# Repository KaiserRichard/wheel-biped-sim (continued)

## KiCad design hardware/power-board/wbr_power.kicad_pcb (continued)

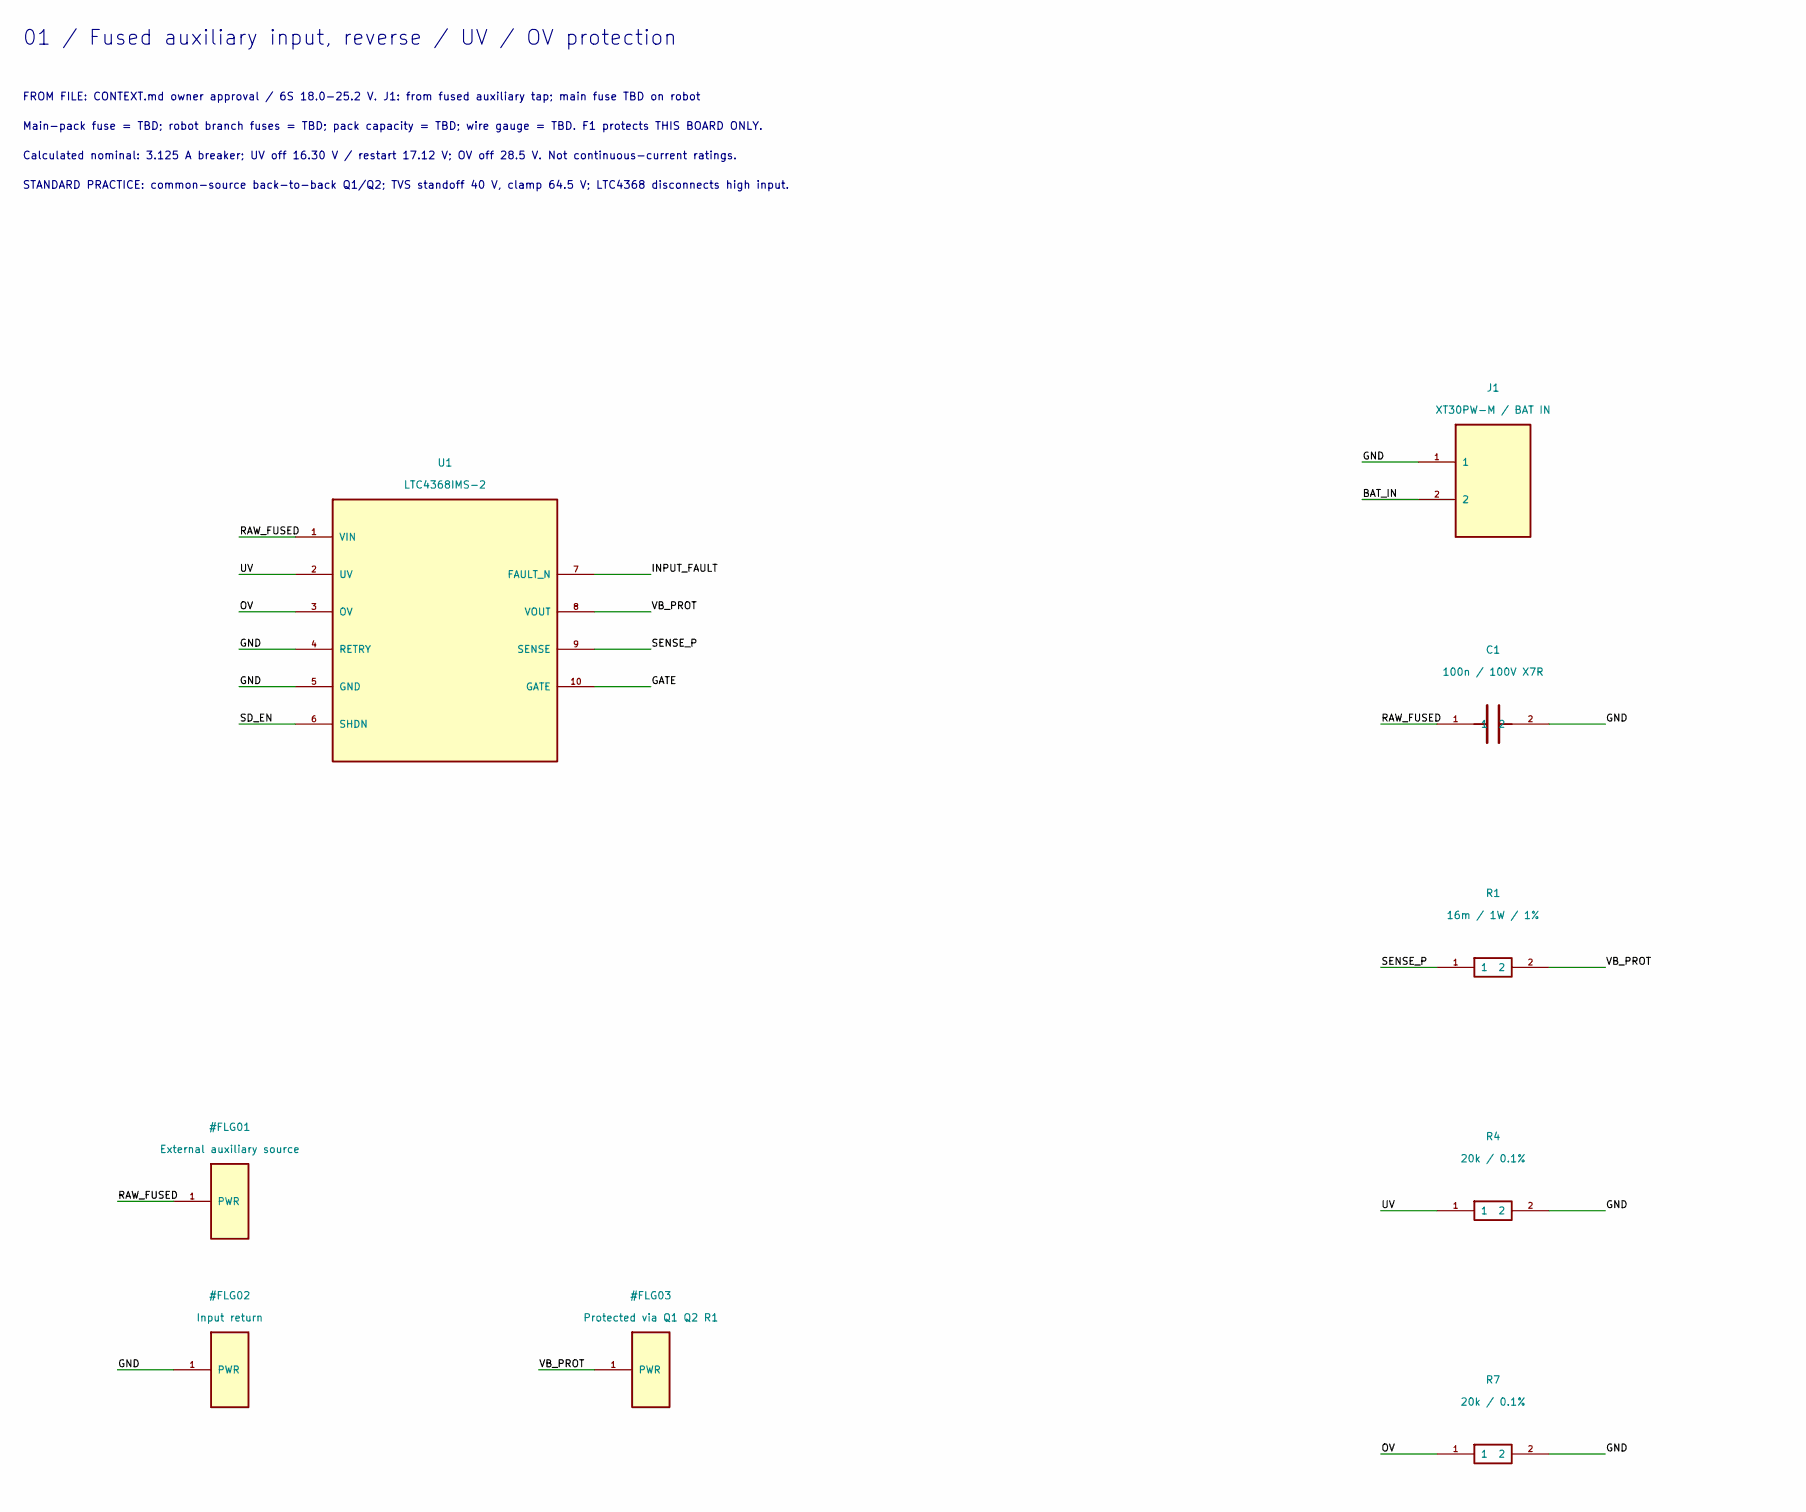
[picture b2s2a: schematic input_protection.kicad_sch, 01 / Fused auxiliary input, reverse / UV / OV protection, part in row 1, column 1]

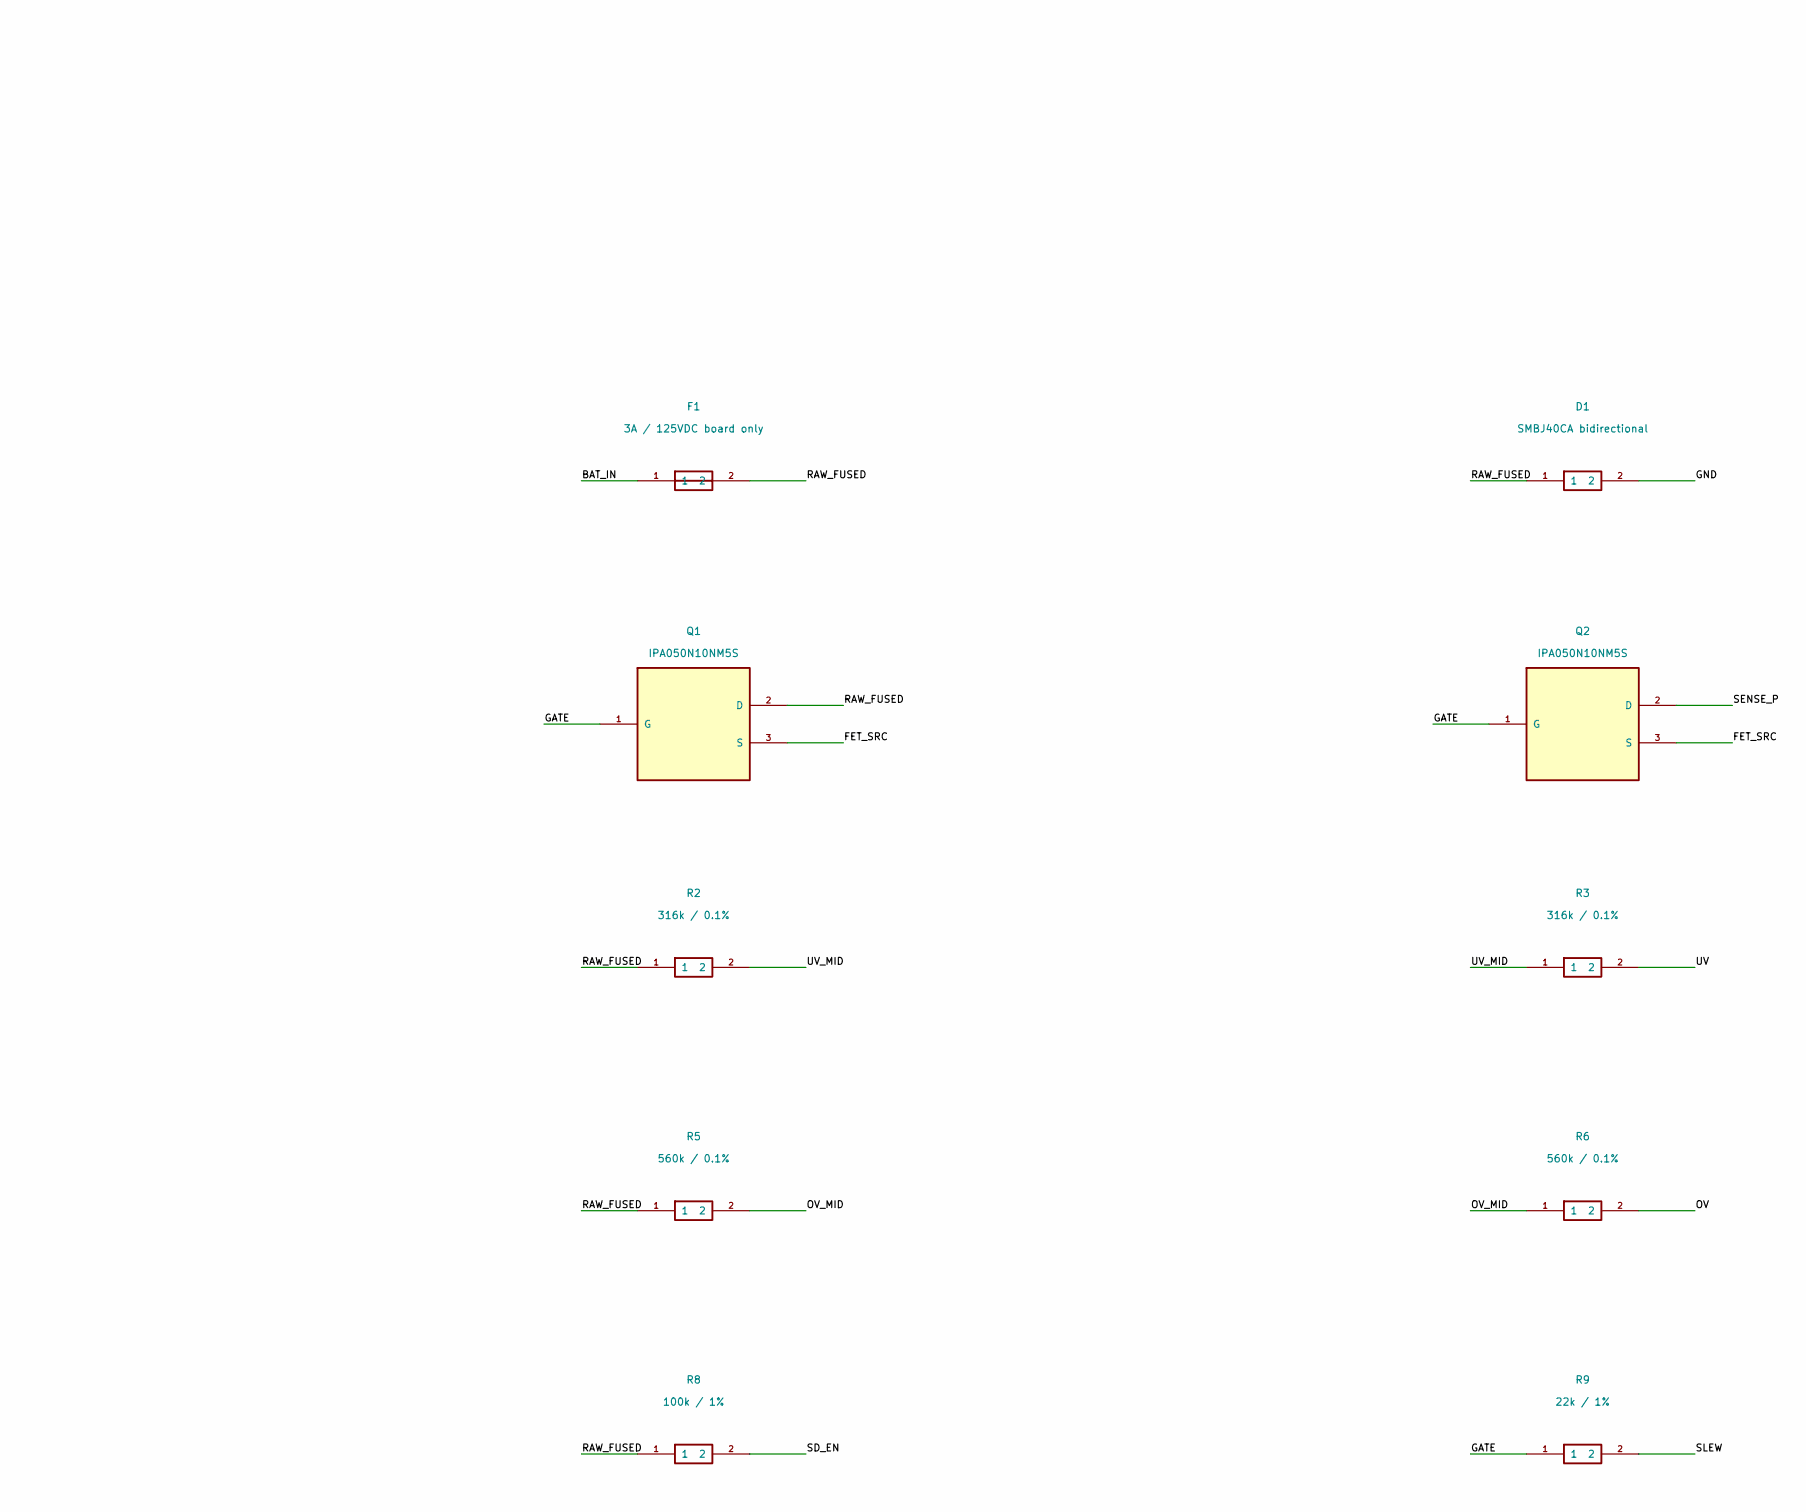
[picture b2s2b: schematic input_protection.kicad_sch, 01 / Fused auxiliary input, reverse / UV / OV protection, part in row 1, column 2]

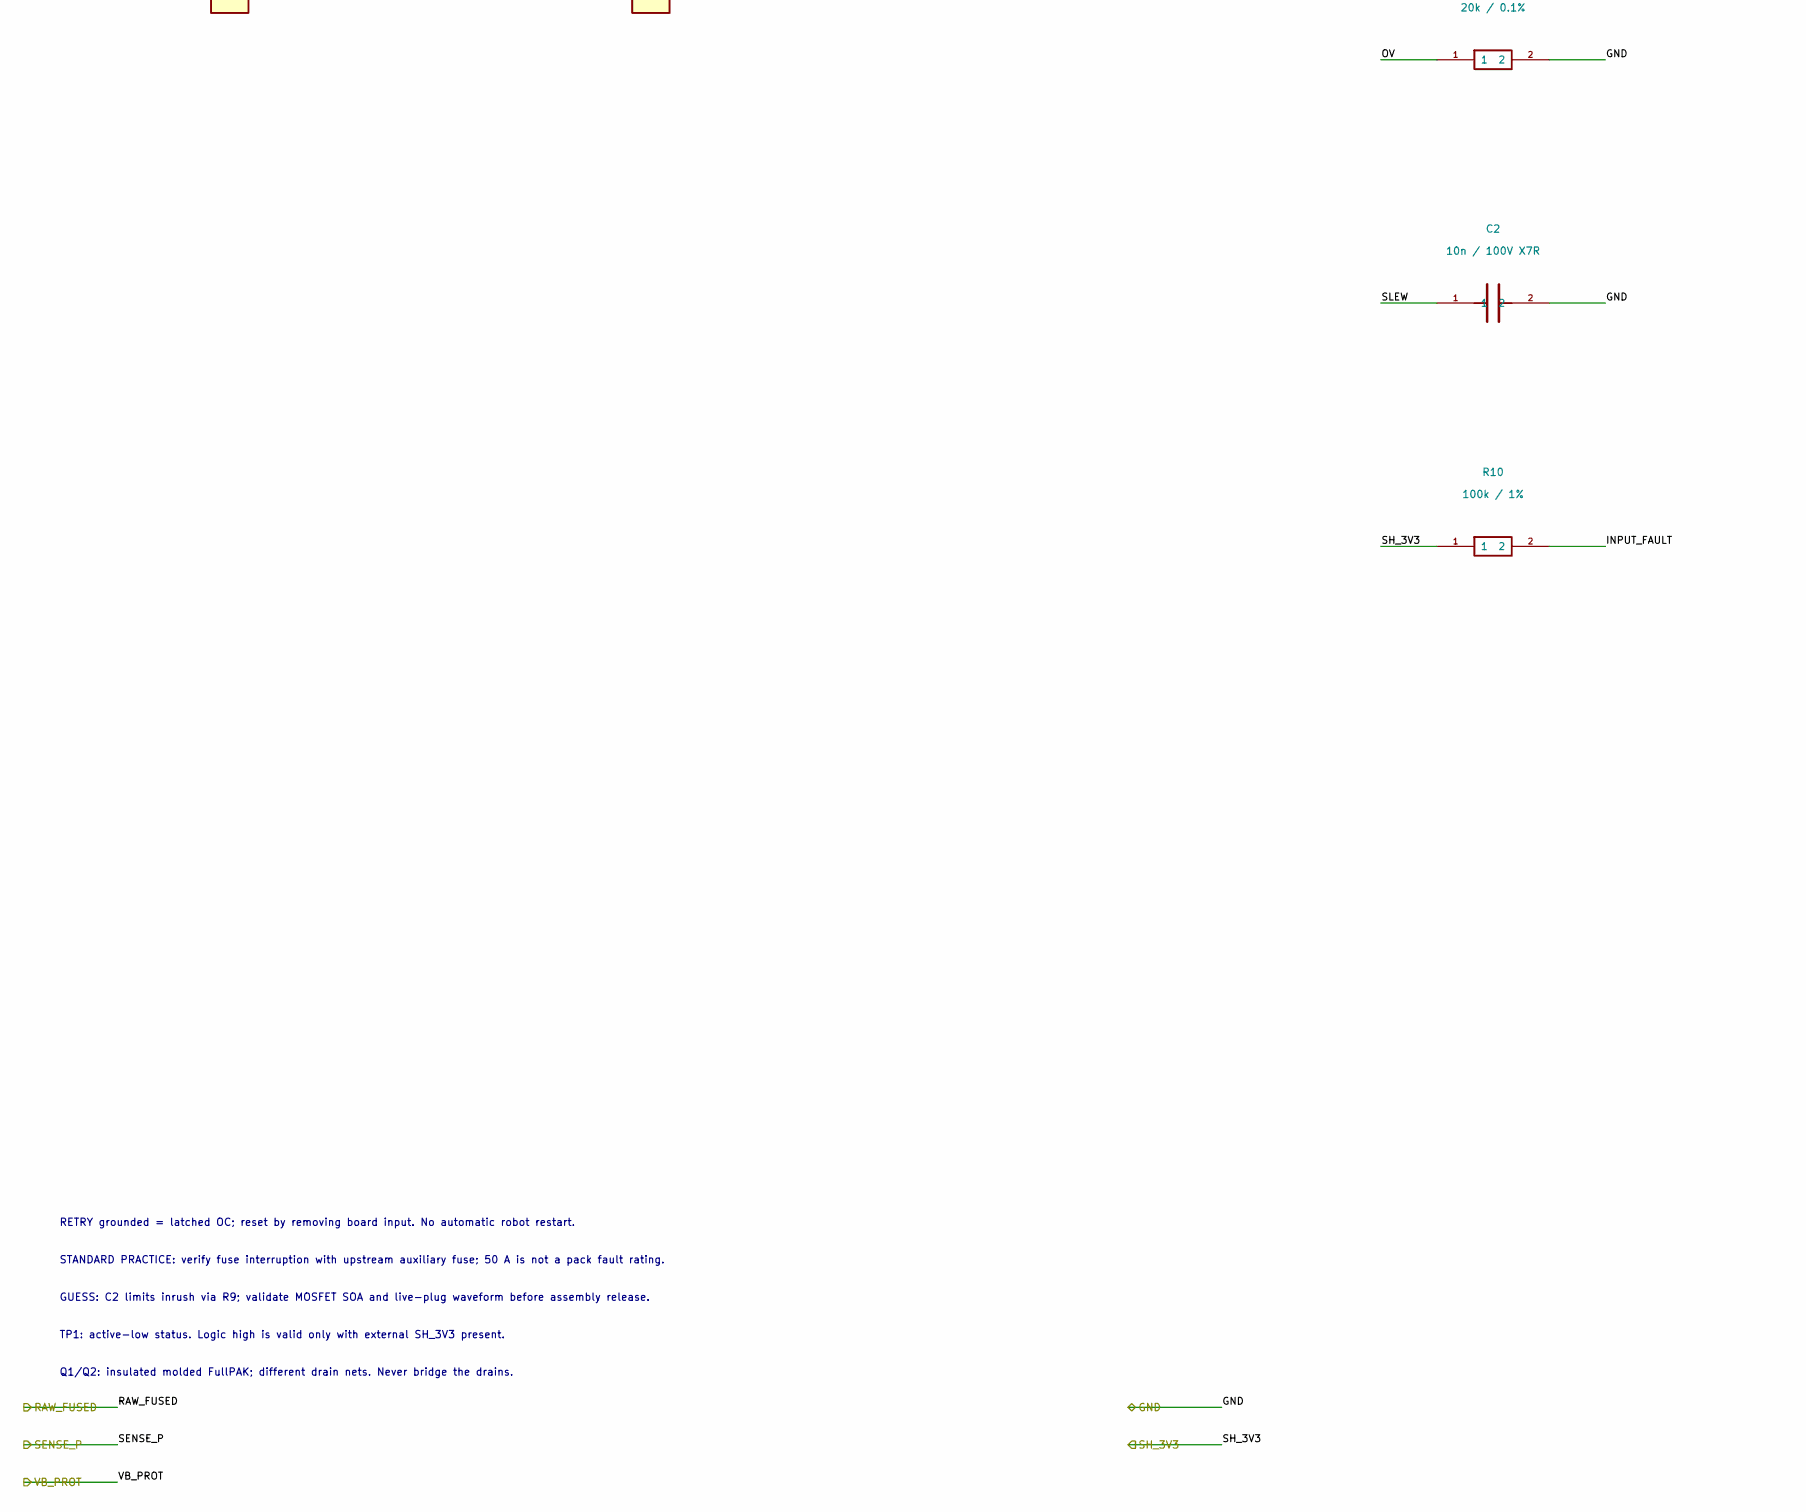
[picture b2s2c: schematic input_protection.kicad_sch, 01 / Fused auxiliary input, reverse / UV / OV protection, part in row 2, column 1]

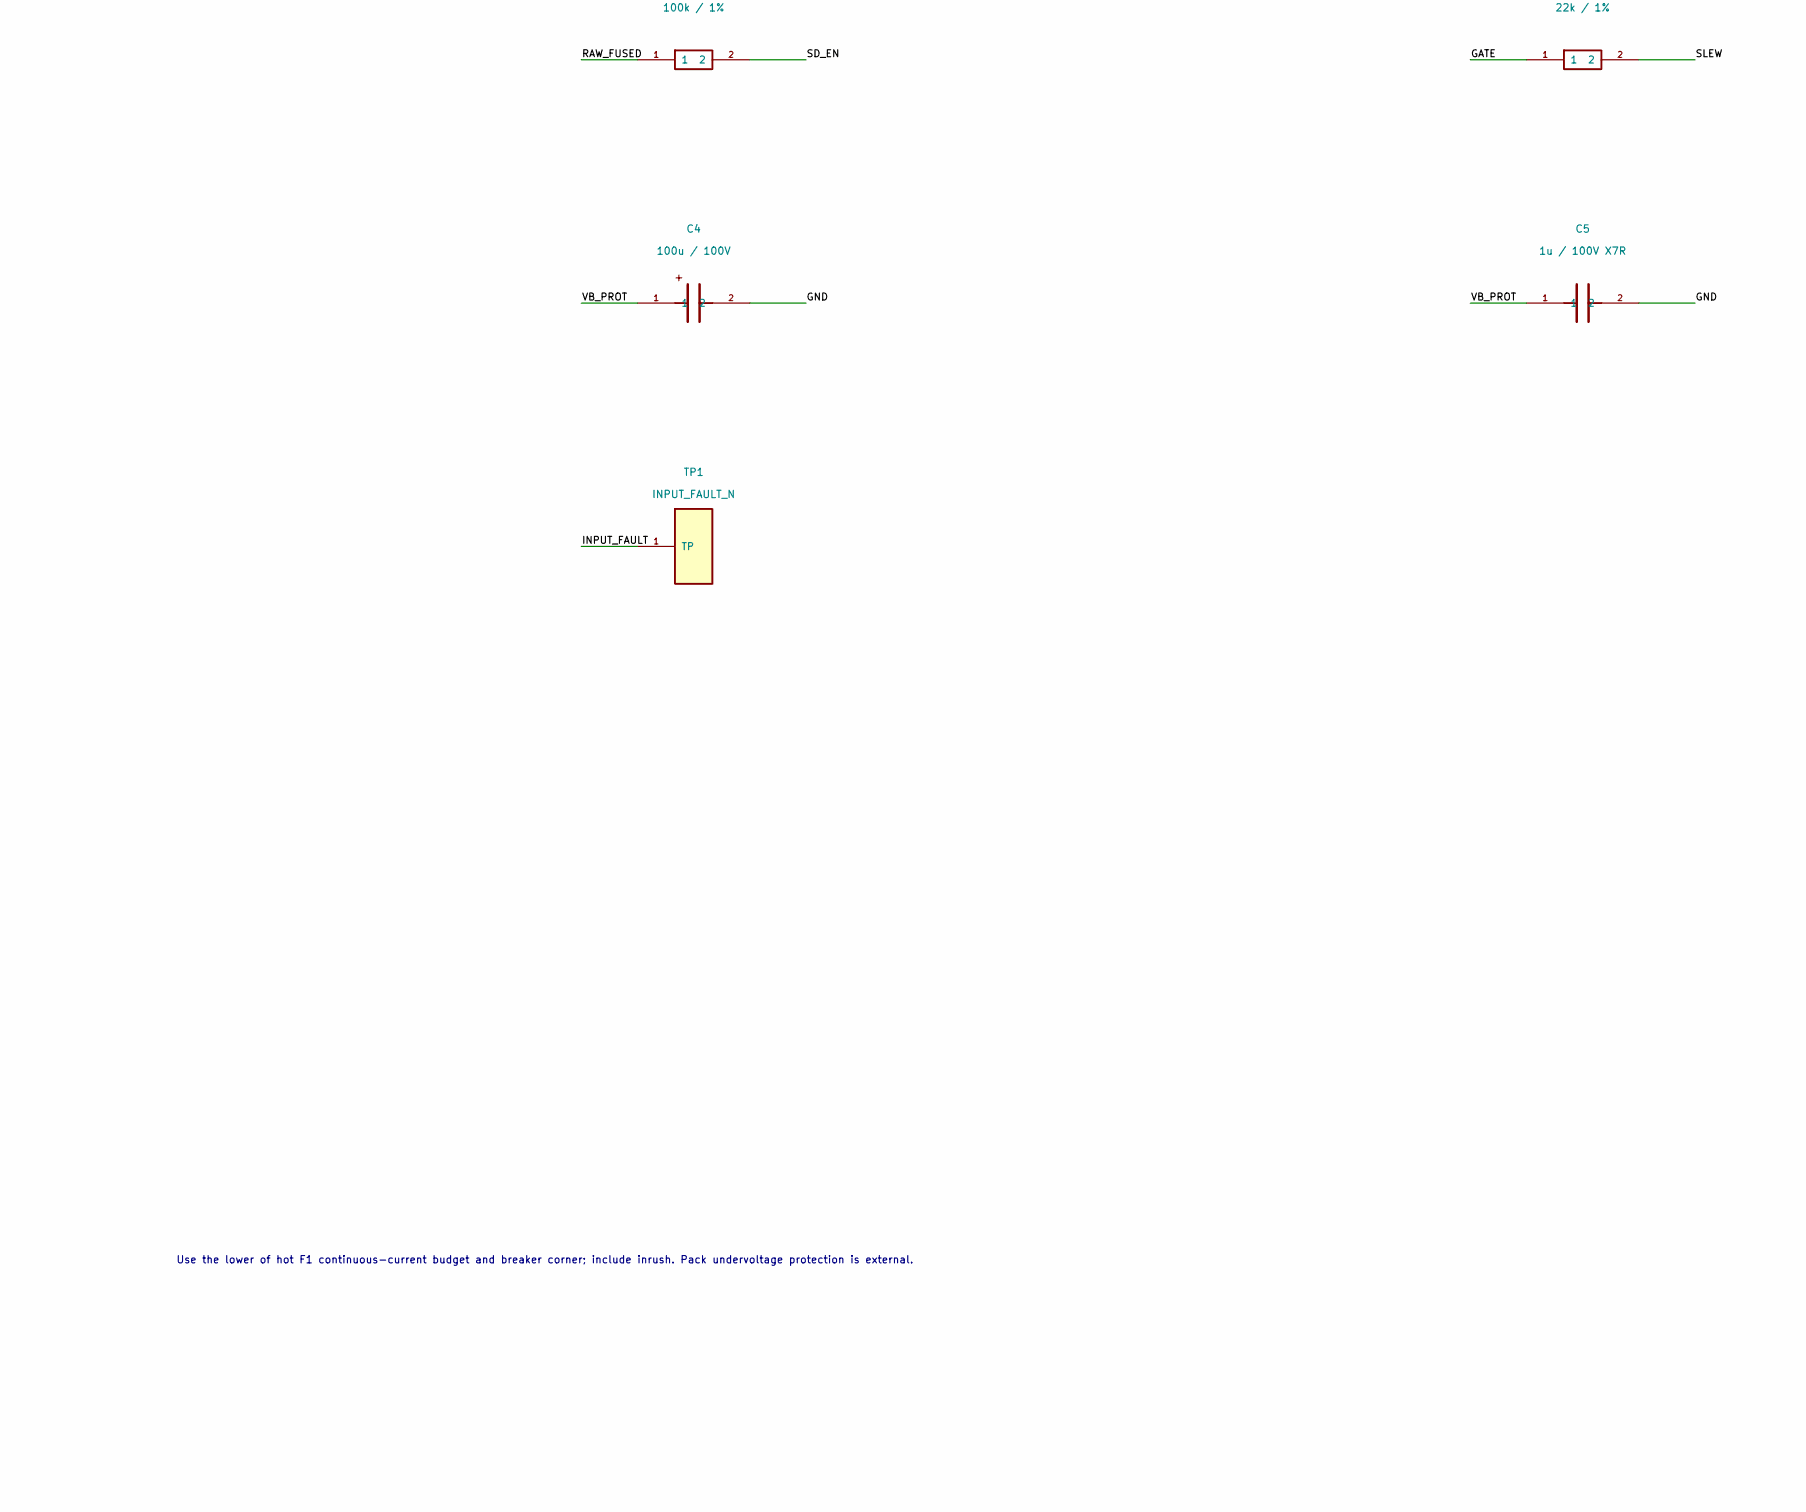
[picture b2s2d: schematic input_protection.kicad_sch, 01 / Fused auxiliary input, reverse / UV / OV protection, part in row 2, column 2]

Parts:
C1: 100n / 100V X7R; C_1206_3216Metric; Rating 100 V; MPN 100n / 100V X7R
C2: 10n / 100V X7R; C_1210_3225Metric; Rating 100 V; MPN 10n / 100V X7R
C4: 100u / 100V; CP_Radial_D10.0mm_P5.00mm; Rating 100 V; polarized + at pin 1; MPN 100u / 100V
C5: 1u / 100V X7R; C_1210_3225Metric; Rating 100 V; MPN 1u / 100V X7R
D1: SMBJ40CA bidirectional; D_SMB; Rating VRWM 40 V; VC 64.5 V at 9.3 A / 10-1000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; MPN SMBJ40CA bidirectional
F1: 3A / 125VDC board only; Fuse_Littelfuse-NANO2-451_453; Rating 125 VDC; 50 A interrupt; MPN Littelfuse 0451003.MRL
J1: XT30PW-M / BAT IN; AMASS_XT30PW-M_1x02_P5.00mm_Horizontal; Rating 500 V; >=3 A; MPN XT30PW-M / BAT IN
Q1, Q2: IPA050N10NM5S; TO-220F-3_Infineon_FullPAK_Vertical; Rating 100 V VDS; 5.0 mOhm max at VGS=10 V, TJ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; MPN IPA050N10NM5S
R1: 16m / 1W / 1%; R_2512_6332Metric; Rating >=75 V element; 1 W; MPN 16m / 1W / 1%
R2, R3: 316k / 0.1%; R_1206_3216Metric; Rating 150 V; MPN 316k / 0.1%
R4, R7: 20k / 0.1%; R_1206_3216Metric; Rating 150 V; MPN 20k / 0.1%
R5, R6: 560k / 0.1%; R_1206_3216Metric; Rating 150 V; MPN 560k / 0.1%
R8, R10: 100k / 1%; R_1206_3216Metric; Rating 150 V; MPN 100k / 1%
R9: 22k / 1%; R_1206_3216Metric; Rating 150 V; MPN 22k / 1%
TP1: INPUT_FAULT_N; TestPoint_Pad_D2.0mm; Rating 3.3 V logic-level test point; requires 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; MPN INPUT_FAULT_N
U1: LTC4368IMS-2; MSOP-10_3x3mm_P0.5mm; Rating VIN -40 to +100 V protection; 60 V norm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; MPN LTC4368IMS-2

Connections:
/GND: C1.2, C2.2, C4.2, C5.2, D1.2, J1.1, R4.2, R7.2, U1.4 (RETRY), U1.5 (GND); also elsewhere on the board
/RAW_FUSED: C1.1, D1.1, F1.2, Q1.2 (D), R2.1, R5.1, R8.1, U1.1 (VIN); also elsewhere on the board
/SENSE_P: Q2.2 (D), R1.1, U1.9 (SENSE); also elsewhere on the board
/SH_3V3: R10.1; also elsewhere on the board
/VB_PROT: C4.1, C5.1, R1.2, U1.8 (VOUT); also elsewhere on the board
/input_protection/BAT_IN: F1.1, J1.2
/input_protection/FET_SRC: Q1.3 (S), Q2.3 (S)
/input_protection/GATE: Q1.1 (G), Q2.1 (G), R9.1, U1.10 (GATE)
/input_protection/INPUT_FAULT: R10.2, TP1.1, U1.7 (FAULT_N)
/input_protection/OV: R6.2, R7.1, U1.3 (OV)
/input_protection/OV_MID: R5.2, R6.1
/input_protection/SD_EN: R8.2, U1.6 (SHDN)
/input_protection/SLEW: C2.1, R9.2
/input_protection/UV: R3.2, R4.1, U1.2 (UV)
/input_protection/UV_MID: R2.2, R3.1

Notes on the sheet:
01 / Fused auxiliary input, reverse / UV / OV protection
FROM FILE: CONTEXT.md owner approval / 6S 18.0-25.2 V. J1: from fused auxiliary tap; main fuse TBD on robot
Main-pack fuse = TBD; robot branch fuses = TBD; pack capacity = TBD; wire gauge = TBD. F1 protects THIS BOARD ONLY.
Calculated nominal: 3.125 A breaker; UV off 16.30 V / restart 17.12 V; OV off 28.5 V. Not continuous-current ratings.
STANDARD PRACTICE: common-source back-to-back Q1/Q2; TVS standoff 40 V, clamp 64.5 V; LTC4368 disconnects high input.
RETRY grounded = latched OC; reset by removing board input. No automatic robot restart.
STANDARD PRACTICE: verify fuse interruption with upstream auxiliary fuse; 50 A is not a pack fault rating.
GUESS: C2 limits inrush via R9; validate MOSFET SOA and live-plug waveform before assembly release.
TP1: active-low status. Logic high is valid only with external SH_3V3 present.
Q1/Q2: insulated molded FullPAK; different drain nets. Never bridge the drains.
Use the lower of hot F1 continuous-current budget and breaker corner; include inrush. Pack undervoltage protection is external.
